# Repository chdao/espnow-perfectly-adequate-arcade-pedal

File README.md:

# ESPNow Perfectly Adequate Arcade Pedal

A wireless pedal system using ESP-NOW for low-latency communication between pedal transmitters and a USB HID keyboard receiver. Perfectly adequate for arcade gaming!

**Original Design**: This project is based on the [Perfectly Adequate Arcade Pedal (Wireless)](https://www.printables.com/model/1220746-perfectly-adequate-arcade-pedal-wireless) design on Printables. All initial ideas and the pedal model come from that design.

**PCB Project**: The custom PCB design is called **PanicPedal Pro** and includes an ESP32-S3-WROOM with automatic pedal detection. See `kicad-pcb/` for the KiCad project files and `esp32/panicpedal-pro/` for the firmware.

**⚠️ IMPORTANT CORRECTION**: The original schematic shows TP4056 OUT+ connected to the 3V3 pin. This is **INCORRECT** and can damage the ESP32. The TP4056 OUT+ must connect to **VCC** instead. See the [Wiring Diagram](#wiring-diagram) section below for the correct connections.

## Overview

This project consists of:
- **Transmitters**: ESP32-based pedal devices that send key press/release events via ESP-NOW
  - **FireBeetle 2**: `esp32/firebeetle2/firebeetle2.ino` - Configurable single or dual pedal mode
  - **PanicPedal Pro**: `esp32/panicpedal-pro/panicpedal-pro.ino` - Custom PCB with automatic pedal detection (1 or 2 pedals)
- **Receiver**: ESP32-S2/S3 device that receives ESP-NOW messages and types keys via USB HID Keyboard (`esp32/receiver/receiver.ino`)

**Note**: `espnow-pedal.cpp` is included as a reference file showing the original implementation. The actual project files are in the `esp32/` directory.

## Features

- **Low latency**: ESP-NOW provides fast, direct communication without WiFi connection
- **Multiple pedal modes**: Supports single pedal (LEFT or RIGHT) or dual pedal configurations
- **Automatic pedal detection** (PanicPedal Pro): Automatically detects whether 1 or 2 pedals are connected using NC (normally-closed) contacts - no manual configuration needed
- **Press and hold**: Keys stay pressed until pedal is released
- **Independent operation**: Both pedals can be pressed simultaneously
- **Battery efficient**: Includes inactivity timeout and deep sleep support
- **Automatic discovery**: No manual MAC address configuration needed - transmitters automatically discover receivers
- **Automatic reconnection**: Transmitters automatically reconnect to receivers after reboot
- **Slot management**: Receiver tracks available slots and only accepts transmitters when slots are available
- **Grace period**: 30-second discovery period after receiver boot for initial pairing and verification

## Hardware Requirements

### Recommended Boards

**Transmitters:**
- [FireBeetle 2 ESP32-E](https://www.dfrobot.com/product-2195.html) - Optimized for low power consumption, ideal for battery-powered pedal transmitters
- **PanicPedal Pro** - Custom PCB project with ESP32-S3-WROOM featuring automatic pedal detection (see `esp32/panicpedal-pro/README.md` for details)

**Receiver:**
- [ESP32-S3-DevKitC-1-N16R8](https://www.amazon.com/dp/B0CC8NYXRG) - ESP32-S3 board with native USB support for HID Keyboard functionality

### Transmitter
- ESP32 (tested with FireBeetle 2 ESP32-E and ESP32-S3-WROOM for PanicPedal Pro)
- Pedal switches (normally-open, connected to GPIO with pull-up)
- Optional: LED for status indication
- **PanicPedal Pro**: Uses NC (normally-closed) contacts for automatic detection of connected pedals

### Receiver
- ESP32-S2 or ESP32-S3 (for USB HID Keyboard support)
- USB connection to computer

## Pin Configuration

### Transmitter
- **Single Pedal Mode**: Connect pedal switch to GPIO 13
- **Dual Pedal Mode**: 
  - LEFT pedal: GPIO 13
  - RIGHT pedal: GPIO 14
- **LED**: GPIO 2 (optional)

**Pinout Reference**: See [FireBeetle 2 ESP32-E Pinout](docs/FireBeetle2_ESP32-E_Pinout.md) for complete pin details.

### Receiver
- Uses USB for communication (no GPIO pins needed for functionality)

## Wiring Diagram

### Transmitter Power Wiring (FireBeetle 2 ESP32-E)

**⚠️ IMPORTANT**: The TP4056 charging board OUT+ must connect to **VCC**, NOT 3V3!

```
TP4056 Charging Board          FireBeetle 2 ESP32-E
─────────────────────          ─────────────────────
OUT+ (red wire)    ──────────> VCC (or PH2.0 battery connector)
OUT- (black wire)  ──────────> GND
B+                 ──────────> 18650 Battery +
B-                 ──────────> 18650 Battery -
IN+                ──────────> Power Switch
IN-                ──────────> GND
```

**Why VCC and not 3V3?**
- **VCC** is the input voltage pin that accepts battery voltage (3.7-4.2V) or USB voltage (~4.7V)
- **3V3** is a regulated 3.3V OUTPUT pin - connecting 4-5V to it can damage the ESP32
- The FireBeetle's onboard regulator converts VCC to 3.3V internally

### Transmitter Signal Wiring

```
Left Pedal Switch (NO)  ───> GPIO 13
Left Pedal Switch (COM) ───> GND

Right Pedal Switch (NO)  ───> GPIO 14 (dual mode only)
Right Pedal Switch (COM) ───> GND

LED (anode)            ───> GPIO 2 (optional)
LED (cathode)          ───> GND
```

**Note**: The original schematic may show a "Mode Select Switch" on GPIO 26 for selecting between Bluetooth and ESP-NOW modes. This code uses ESP-NOW only, so that switch is not needed. Pedal mode (single/dual) is configured via the `PEDAL_MODE` define in the code.

**Note**: Switches should be normally-open (NO) type. The ESP32's internal pull-up resistors keep the pins HIGH when switches are open, and LOW when pressed.

## Setup and Usage

For detailed setup instructions, usage guide, configuration options, debug monitor setup, and troubleshooting, see [INSTRUCTIONS.md](INSTRUCTIONS.md).

## License

This project is provided as-is for educational and personal use.

## Contributing

Feel free to submit issues or pull requests for improvements!

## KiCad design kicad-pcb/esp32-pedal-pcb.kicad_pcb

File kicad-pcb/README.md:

# ESP32 Pedal PCB Design

KiCad project for a custom ESP32-based pedal PCB.

⚠️ **UNTESTED** - This is a design-only PCB that has not been manufactured or tested.

## Images

*Complete schematic diagram*

*PCB layout and routing*

*3D visualization of the PCB*

*Reference: FireBeetle 2 ESP32-E board (for comparison)*

## Design Files

All design files are included in this directory:
- `esp32-pedal-pcb.kicad_pro` - KiCad project file
- `esp32-pedal-pcb.kicad_sch` - Schematic
- `esp32-pedal-pcb.kicad_pcb` - PCB layout
- `esp32-pedal-pcb.kicad_dru` - Design rules
- `esp32-pedal-pcb.rules` - Custom design rules
- `esp32-pedal-pcb.csv` - Bill of Materials (BOM)

## Notes

- KiCad 7.0 or later required
- Custom Espressif symbol and footprint libraries included in this directory
- Design files are tracked in git (temporary files excluded via `.gitignore`)

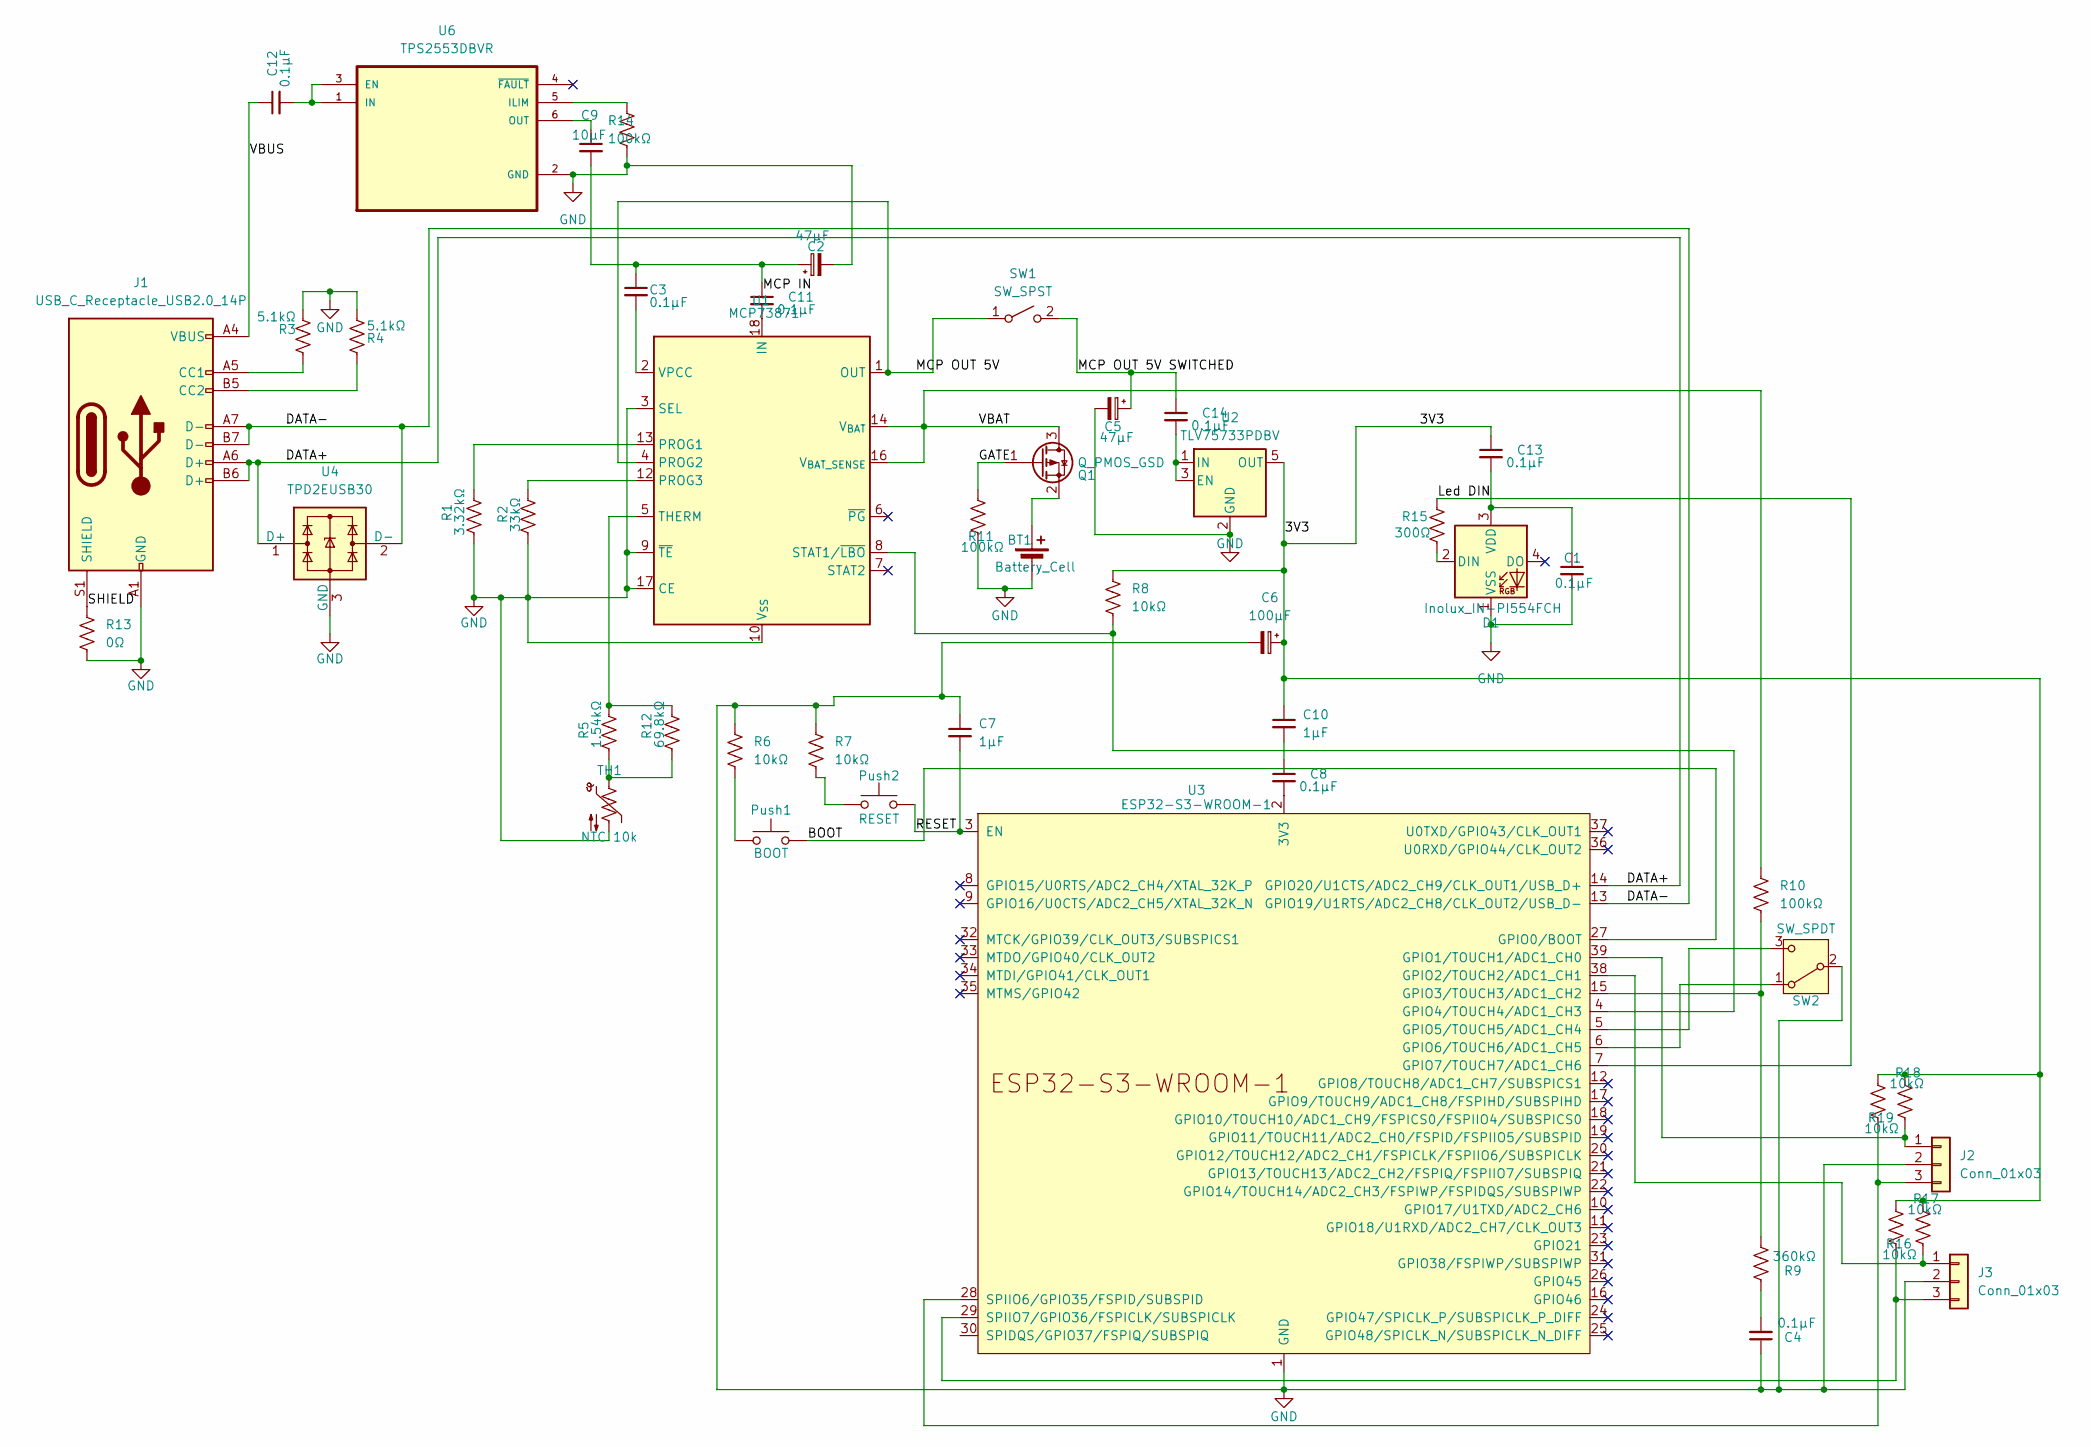
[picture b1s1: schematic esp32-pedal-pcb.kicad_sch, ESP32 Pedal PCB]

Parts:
BT1: Battery_Cell; BatteryHolder_MPD_BH-18650-PC
C1, C3, C4, C8, C11, C12, C13, C14: 0.1µF; C_0603_1608Metric
C2, C5: 47µF; CP_EIA-7343-31_Kemet-D
C6: 100µF; CP_EIA-7343-31_Kemet-D
C7, C10: 1µF; C_0603_1608Metric
C9: 10µF; C_0603_1608Metric
D1: Inolux_IN-PI554FCH; LED_Inolux_IN-PI554FCH_PLCC4_5.0x5.0mm_P3.2mm
J1: USB_C_Receptacle_USB2.0_14P; USB_C_Receptacle_GCT_USB4110
J2, J3: Conn_01x03; SolderWire-0.1sqmm_1x03_P3.6mm_D0.4mm_OD1mm
Push1: BOOT; SW_Push_1P1T_XKB_TS-1187A
Push2: RESET; SW_Push_1P1T_XKB_TS-1187A
Q1: Q_PMOS_GSD; SOT-23
R1: 3.32kΩ; R_0603_1608Metric
R2: 33kΩ; R_0603_1608Metric
R3, R4: 5.1kΩ; R_0603_1608Metric
R5: 1.54kΩ; R_0603_1608Metric
R6, R7, R8, R16, R17, R18, R19: 10kΩ; R_0603_1608Metric
R9: 360kΩ; R_0603_1608Metric
R10, R11, R14: 100kΩ; R_0603_1608Metric
R12: 69.8kΩ; R_0603_1608Metric
R13: 0Ω; R_0603_1608Metric
R15: 300Ω; R_0603_1608Metric
SW1: SW_SPST; SolderWire-0.1sqmm_1x02_P3.6mm_D0.4mm_OD1mm
SW2: SW_SPDT; SolderWire-0.1sqmm_1x03_P3.6mm_D0.4mm_OD1mm
TH1: NTC 10k; SolderWire-0.1sqmm_1x02_P3.6mm_D0.4mm_OD1mm
U1: MCP73871; QFN-20-1EP_4x4mm_P0.5mm_EP2.5x2.5mm
U2: TLV75733PDBV; SOT-23-5
U3: ESP32-S3-WROOM-1
U4: TPD2EUSB30; Texas_DRT-3
U6: TPS2553DBVR; SOT95P280X145-6N

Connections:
/3V3: C6.1, C10.1, C13.1, R8.1, R16.1, R17.1, R18.1, R19.1, U2.5 (OUT)
/BOOT: Push1.2, U3.27 (GPIO0/BOOT)
/DATA+: J1.A6 (D+), J1.B6 (D+), U3.14 (GPIO20/U1CTS/ADC2_CH9/CLK_OUT1/USB_D+), U4.1 (D+)
/DATA-: J1.A7 (D-), J1.B7 (D-), U3.13 (GPIO19/U1RTS/ADC2_CH8/CLK_OUT2/USB_D-), U4.2 (D-)
/GATE: Q1.1 (G), R11.1
/Led DIN: R15.1, U3.7 (GPIO7/TOUCH7/ADC1_CH6)
/MCP OUT 5V: SW1.1 (A), U1.1 (OUT), U1.4 (PROG2), U1.20 (OUT)
/MCP OUT 5V SWITCHED: C5.1, C14.1, SW1.2 (B)
/RESET: C7.2, Push2.2, U3.3 (EN)
/SHIELD: J1.S1 (SHIELD), R13.1
/VBAT: Q1.3 (D), R10.1, U1.14 (V_{BAT}), U1.15 (V_{BAT}), U1.16 (V_{BAT_SENSE})
/VBUS: C12.1, J1.A4 (VBUS), J1.A9 (VBUS), J1.B4 (VBUS), J1.B9 (VBUS)
GND: BT1.2 (-), C1.2, C2.2, C4.1, C5.2, C6.2, C7.1, D1.1 (VSS), J1.A1 (GND), J1.A12 (GND), J1.B1 (GND), J1.B12 (GND), J2.2, J3.2, R1.2, R2.2, R3.1, R4.1, R6.1, R7.1, R11.2, R13.2, R14.2, SW2.2 (B), TH1.2, U1.3 (SEL), U1.9 (~TE), U1.10 (V_{SS}), U1.11 (V_{SS}), U1.17 (CE), U1.21 (V_{SS}), U2.2 (GND), U3.1 (GND), U3.40 (GND), U3.41 (GND), U4.3 (GND), U6.2 (GND)
unnamed: BT1.1 (+), Q1.2 (S)
unnamed: C4.2, R9.1
unnamed: C8.1, C10.2
unnamed: C2.1, C3.1, C9.2, C11.1
unnamed: C11.2, U1.18 (IN), U1.19 (IN)
unnamed: D1.2 (DIN), R15.2
unnamed: C1.1, C13.2, D1.3 (VDD)
unnamed: J1.A5 (CC1), R3.2
unnamed: J1.B5 (CC2), R4.2
unnamed: J2.1, R18.2, U3.39 (GPIO1/TOUCH1/ADC1_CH0)
unnamed: J2.3, R19.2, U3.28 (SPIIO6/GPIO35/FSPID/SUBSPID)
unnamed: J3.1, R17.2, U3.38 (GPIO2/TOUCH2/ADC1_CH1)
unnamed: J3.3, R16.2, U3.29 (SPIIO7/GPIO36/FSPICLK/SUBSPICLK)
unnamed: Push1.1, R6.2
unnamed: Push2.1, R7.2
unnamed: R5.2, R12.2, TH1.1
unnamed: SW2.1 (A), U3.6 (GPIO6/TOUCH6/ADC1_CH5)
unnamed: SW2.3 (C), U3.5 (GPIO5/TOUCH5/ADC1_CH4)
unnamed: R1.1, U1.13 (PROG1)
unnamed: R2.1, U1.12 (PROG3)
unnamed: R8.2, U1.8 (STAT1/~LBO), U3.4 (GPIO4/TOUCH4/ADC1_CH3)
unnamed: R5.1, R12.1, U1.5 (THERM)
unnamed: C3.2, U1.2 (VPCC)
unnamed: C14.2, U2.1 (IN), U2.3 (EN)
unnamed: C8.2, U3.2 (3V3)
unnamed: R9.2, R10.2, U3.15 (GPIO3/TOUCH3/ADC1_CH2)
unnamed: C12.2, U6.1 (IN), U6.3 (EN)
unnamed: R14.1, U6.5 (ILIM)
unnamed: C9.1, U6.6 (OUT)

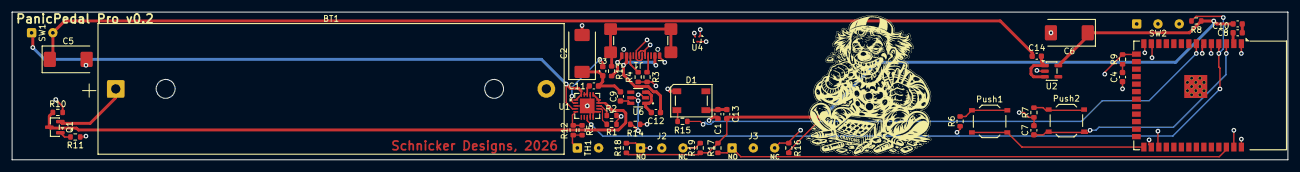
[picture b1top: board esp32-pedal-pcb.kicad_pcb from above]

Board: 4 copper layers, 216.0 x 25.0 mm, 49 parts (0 on the bottom side), 42 nets.

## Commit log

2025-12-31 Remove .theia directory from repository and add to .gitignore
2025-12-31 Update README: clarify that espnow-pedal.cpp is reference file
2025-12-31 Update README: Add detailed MAC address configuration instructions
2025-12-31 Add run-this-first.ino helper sketch to easily get receiver MAC address
2025-12-31 Fix MAC address output format to match transmitter (lowercase hex)
2025-12-31 Simplify MAC address output using helper function
2025-12-31 Fix helper function to correctly print hex values
2025-12-31 Optimize transmitter code: reduce duplication and simplify logic
2025-12-31 Add link to original Printables design and credit
2026-01-01 Remove GPIO 26 Mode Select Switch reference - not used in ESP-NOW only code
2026-01-01 Add FireBeetle 2 ESP32-E pinout reference documentation
2026-01-01 Add FireBeetle 2 ESP32-E pinout diagram image
2026-01-01 Move MAC address helper to subdirectory and update pinout docs
2026-01-01 Add heartbeat mechanism with exponential backoff and implicit heartbeats
    - Receiver sends alive messages every 30 seconds to paired transmitters
    - Transmitters detect connection loss if no message received for 35 seconds
    - Any message from receiver resets alive timer (implicit heartbeat)
    - Exponential backoff for reconnection: 5s, 10s, 20s, 30s (max)
    - Improved battery efficiency with longer intervals
    - First boot discovery times out after 10s to save battery
2026-01-02 Update README with automatic discovery and reconnection features
    - Document automatic discovery via beacons
    - Explain automatic reconnection after reboot
    - Remove manual MAC address configuration steps
    - Add grace period and LED status indicator documentation
    - Update troubleshooting section with new pairing/reconnection info
    - Simplify setup instructions
2026-01-02 Reduce paired delay to 10ms for better pedal responsiveness
2026-01-02 Add debug monitor documentation to README
    - Document ESP-NOW debug monitor feature
    - Explain how to set up and use debug monitor
    - Update troubleshooting section
    - Fix IDLE_DELAY_PAIRED default value (10ms)
2026-01-02 Check for free slots before sending MSG_ALIVE on transmitter online
    - Receiver now checks if it has free slots before responding to MSG_TRANSMITTER_ONLINE
    - Prevents pairing attempts when receiver is full (no available slots)
    - Known transmitters will not receive MSG_ALIVE if receiver is at capacity
2026-01-02 Fix debug monitor communication and add comprehensive receiver debug messages
    - Fixed receiver debug monitor pairing: now sends status on first beacon after boot
    - Added statusSent flag to prevent duplicate status messages
    - Fixed debug monitor message reception: handle variable-length messages correctly
    - Added detailed debug messages for receiver events:
    * Transmitter online/offline with context (known/unknown, slots available)
    * Discovery requests with pairing success/failure reasons
2026-01-02 Refactor: Move DebugMonitor to shared/ to eliminate code duplication
    - Created shared/DebugMonitor.h and shared/DebugMonitor.cpp
    - Removed duplicate files from transmitter/infrastructure/ and receiver/infrastructure/
    - Abstracted transport layer using function pointers for send/addPeer operations
    - Added callback support for custom status messages (used by receiver)
    - Reduced codebase by ~300 lines while maintaining all functionality
    - Both transmitter and receiver now use the same debug infrastructure
2026-01-02 Refactor: Move DebugMonitor to shared/ with symlinks
    - Created shared/DebugMonitor.h and shared/DebugMonitor.cpp as single source of truth
    - Added symlinks in receiver/shared/ and transmitter/shared/ pointing to shared/
    - Removed duplicate DebugMonitor files from infrastructure directories
    - Abstracted transport layer using function pointers
    - Added callback support for custom status messages
    - Reduced codebase by ~300 lines while maintaining all functionality
2026-01-02 Update README with Windows Developer Mode requirement for symlinks
2026-01-02 Add debug messages for MSG_ALIVE sent on boot
2026-01-02 Add receiver boot ping and deep sleep wake handling
    Receiver improvements:
    - Sends MSG_ALIVE to all known transmitters immediately on boot
    - Shows MAC address being pinged in debug messages
    - Helps transmitters reconnect faster without waiting for periodic pings
    Transmitter improvements:
    - Replies to MSG_ALIVE from paired receiver with acknowledgment
2026-01-02 Split documentation: README for overview, INSTRUCTIONS for detailed setup
    - README.md: Concise project overview, features, quick start
    - INSTRUCTIONS.md: Complete setup, wiring, configuration, troubleshooting
    - Improved navigation with clear links between documents
    - Better presentation for GitHub project page
2026-01-02 Update hardware requirements: clarify tested boards vs compatibility
    - Changed 'Recommended' to 'Required/Tested' for accuracy
    - Specify board-specific features (pin 27 button, WS2812 LED)
    - Note that other boards need code modifications
    - Make it clear which features depend on specific hardware
2026-01-02 Add RTC memory persistence for instant resume from deep sleep
    Added:
    - RTC memory persistence for pairing state (survives deep sleep, not power cycles)
    - Transmitter restores pairing from RTC memory on wake from deep sleep
    - Instant resume with no reconnection delay or broadcast
    - Receiver adds peer immediately when pairing is restored
    - Debug messages showing RTC pairing save/restore operations
2026-01-02 Improve debug output and monitoring
    Changed:
    - Simplified startup messages to single 'Ready' message
    - Added debug mode status to transmitter startup output
    - Send 'Ready' message immediately if already paired (not waiting for beacon)
    - Increased debug monitor serial buffer to 8192 bytes for better burst handling
    - Added inactivity timeout diagnostic logging (every 30s when debug enabled)
2026-01-02 Convert debug time displays from milliseconds to seconds
    Changed:
    - Inactivity timeout messages now show seconds with one decimal place
    - Example: '120000 ms' -> '120.0s' or '30000 ms' -> '30.0s'
    - More human-readable debug output
2026-01-04 Fix deep sleep wake-up issues and improve debug monitor reliability
    - Fix first pedal press after deep sleep wake not typing (key validation issue)
    - Fix double release events after wake-up
    - Add cumulative timestamp tracking across deep sleep cycles
    - Add message queue to debug monitor to prevent message loss/corruption
    - Add validation and error logging for invalid key values
    - Rename HEARTBEAT_INTERVAL to DEBUG_STATUS_INTERVAL for clarity
2026-01-04 Add KiCad design rules and DRC files (.kicad_dru, .rules)
2026-01-04 Add images to PCB design documentation
2026-01-04 Add PCB design images to docs folder
2026-01-04 Add README to docs directory
2026-01-04 Add GPIO21 pedal switch to FireBeetle pinout documentation
2026-01-04 Add GPIO21 pedal switch to PCB design documentation (not FireBeetle)
2026-01-05 Update PCB design, documentation, and images
2026-01-05 Simplify PCB README to just link images
2026-01-05 Sync shared messages.h files to include all utilities
2026-01-05 Convert shared directories to symlinks pointing to top-level shared/
2026-01-07 Update PCB schematics and routing, add PCBWAY directory to gitignore
2026-01-08 Remove gerber files from repository and add to gitignore
2026-01-08 Remove KiCad autosave files from repository
2026-01-08 Update BOM
2026-01-08 Add README for PanicPedal Pro transmitter PCB
2026-01-08 Update PanicPedal Pro to support dual pedals (GPIO7 and GPIO21)
2026-01-08 Add automatic switch detection for PanicPedal Pro using NC contacts
    - Add GPIO45 and GPIO46 definitions for NC contacts
    - Implement detectPedalMode() function to auto-detect connected switches
    - Automatically set pedal mode based on detected switches:
    - Both switches connected -> Dual mode
    - Only first switch connected -> Single mode
    - Remove need to hardcode pedal configuration
2026-01-08 Store detected pedal mode in NVRAM for PanicPedal Pro
    - Add Preferences library for NVS storage
    - Store detected pedal mode in NVS on first boot
    - Load stored mode from NVS on subsequent boots
    - Detection runs only once until firmware is reflashed
    - Prevents re-detection on every boot for better reliability
2026-01-08 Add version.h to .gitignore
2026-01-08 Change PanicPedal Pro to detect pedals on every boot
    - Remove NVS storage for pedal mode
    - Remove firmware version checking
    - Run pedal detection on every boot instead of storing
    - Simplifies code and ensures correct configuration even if switches change
    - Update README to reflect new behavior
2026-01-08 Update GPIO pin references in comments and debug output
2026-01-08 Update KiCad PCB project files and backups
2026-01-09 Move setup and usage instructions to INSTRUCTIONS.md
    - Create INSTRUCTIONS.md with all setup, usage, configuration, and troubleshooting content
    - Update README.md to reference INSTRUCTIONS.md instead of including full instructions
    - Keep README focused on overview, features, and hardware requirements
2026-01-09 Update PanicPedal Pro GPIO pin assignments
    - GPIO1: Pedal Left NO (unchanged)
    - GPIO2: Pedal Right NO (unchanged)
    - GPIO3: Battery voltage sensing (unchanged)
    - GPIO4: STAT1/LBO from MCP73871 (unchanged)
    - GPIO5: SPDT switch position 1 (unchanged)
    - GPIO6: SPDT switch position 2 (unchanged)
2026-01-09 Update README to document LED control implementation
2026-01-09 Update README with new LED behavior (off after pairing, only on when charging)
